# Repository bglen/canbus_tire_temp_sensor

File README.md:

# canbus_tire_temp_sensor

Tire temperature sensing with IR sensor arrays and a CAN bus interface

### To Do
* CAD enclosure
* CAN Message Data Frame Description
* Firmware
* Adjust PCB design for PCBA

## Building the Hardware
The gerber files for ordering boards can be found in the /production/ folder. A Digikey List for easy BOM ordering can be found [here](https://www.digikey.com/en/mylists/list/VY1O0SBB26).

## Usage
This device outputs thermal camera data to CAN bus. It does not include termination resistors, so only include it at the beginning or end of the network with an external 120 ohm termination resistor.

### Pinout

| Pin Number | Name     | Description                 |
| ---------- | -------- | --------------------------- |
| 1          | VCC      | Input voltage, 4.5 - 40 VDC |
| 2          | GND      | Ground                      |
| 3          | CAN_N    | CAN bus low                 |
| 4          | CAN_P    | CAN bus high                |

### Default CAN Message IDs

| Default ID     | Message            | Description                                 |
| -------------- | ------------------ | ------------------------------------------- |
| 0x700 + 1,2,3  | Data Messages      | TBD                                         |
| 0x710          | Config Messages    | Adjust Default ID, bitrate, sensor settings |

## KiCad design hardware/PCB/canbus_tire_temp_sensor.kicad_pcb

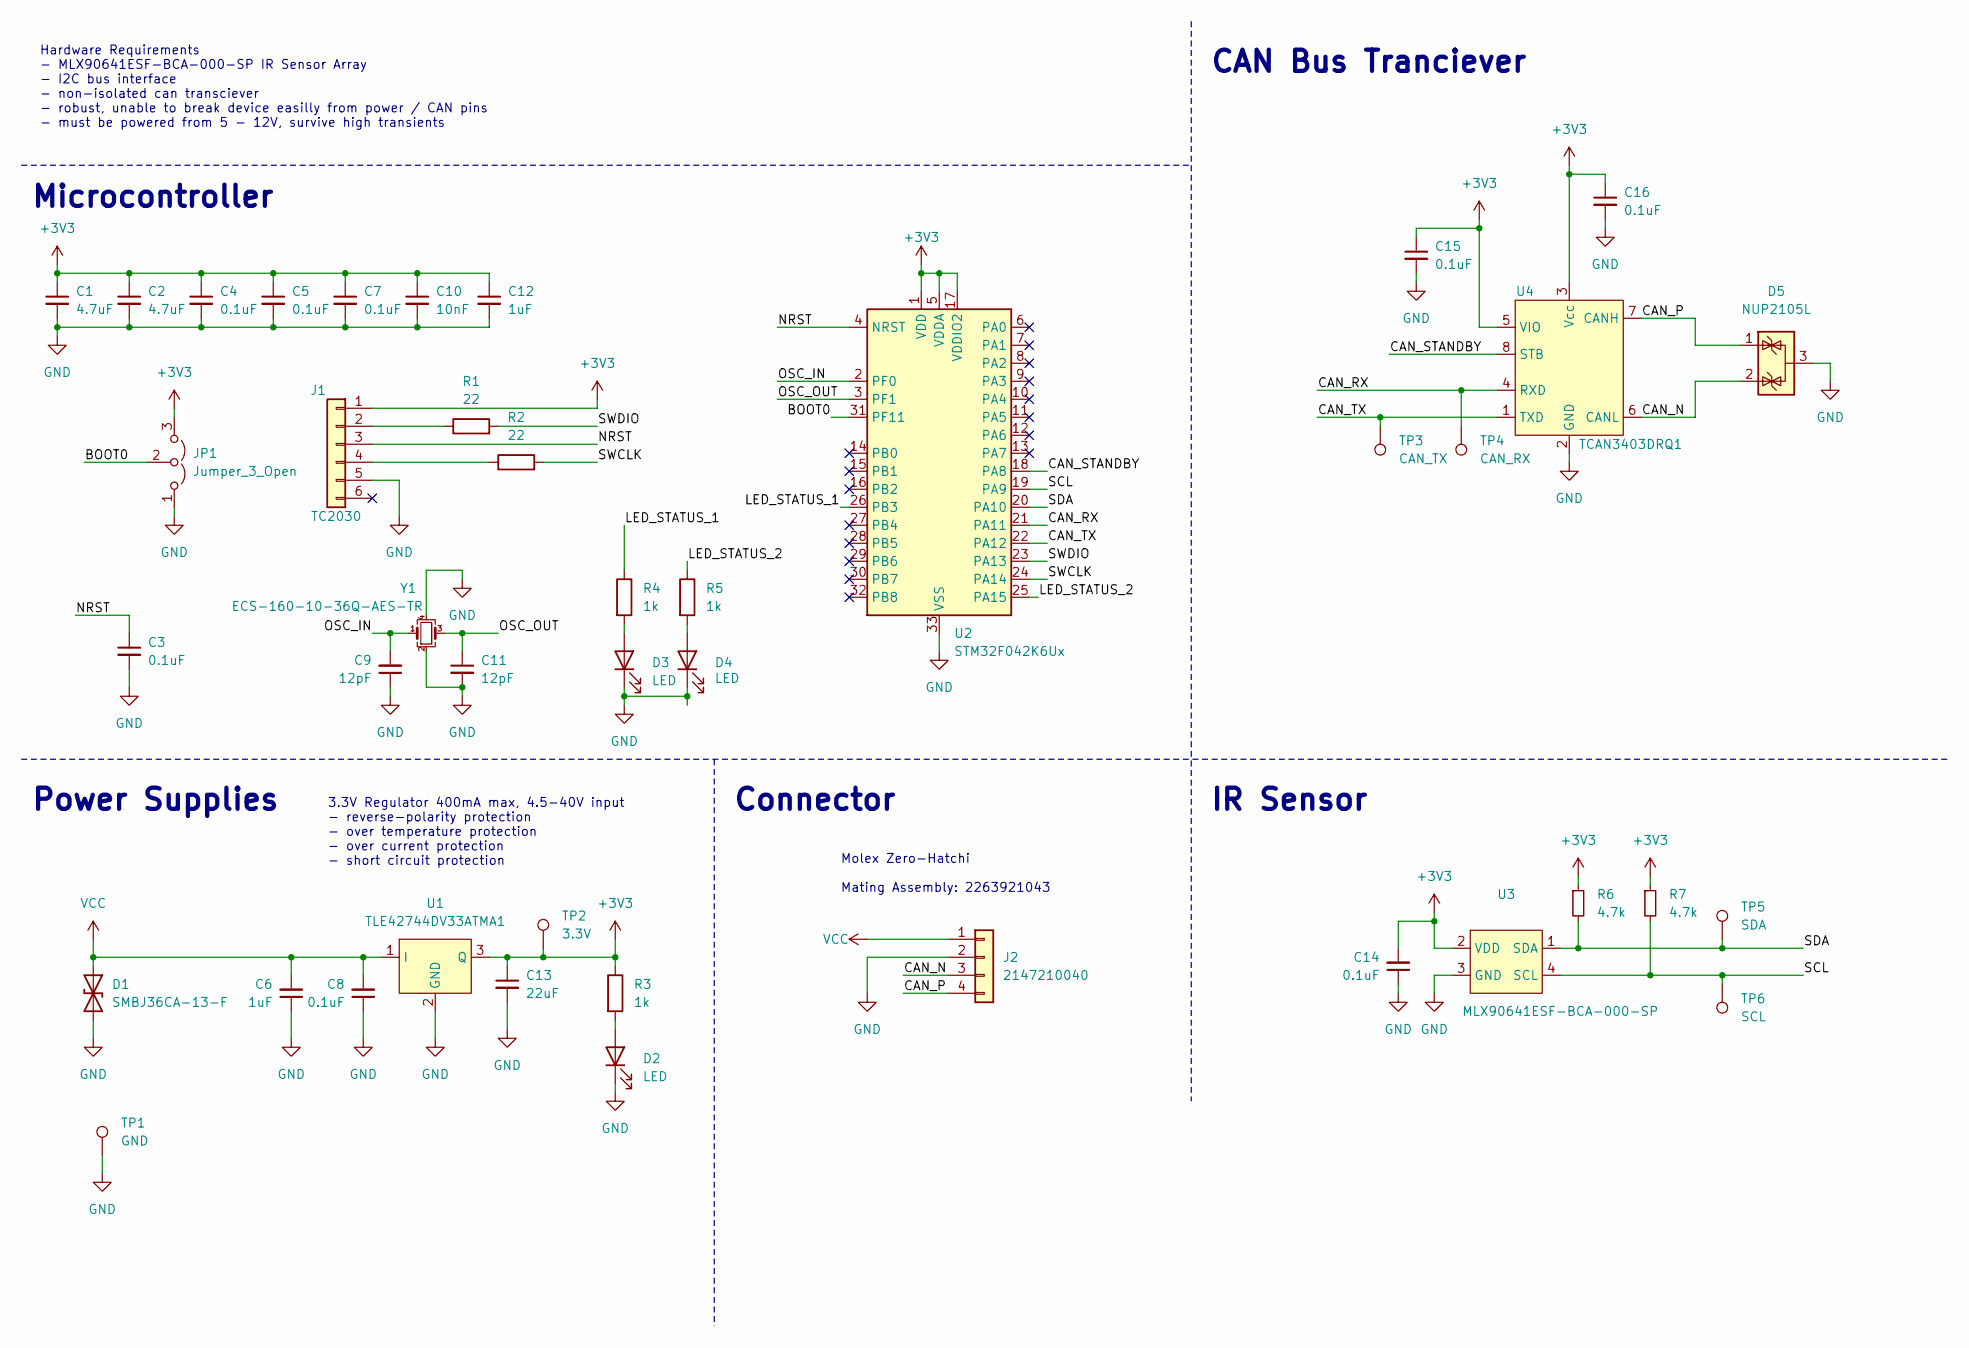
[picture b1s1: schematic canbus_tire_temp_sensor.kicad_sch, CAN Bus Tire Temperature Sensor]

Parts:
C1, C2: 4.7uF; C_0603_1608Metric
C3, C4, C5, C7, C8, C14, C15, C16: 0.1uF; C_0603_1608Metric
C6, C12: 1uF; C_0603_1608Metric
C9, C11: 12pF; C_0603_1608Metric
C10: 10nF; C_0603_1608Metric
C13: 22uF; C_0805_2012Metric
D1: SMBJ36CA-13-F; D_SMB
D2, D3, D4: LED; LED_0603_1608Metric
D5: NUP2105L; SOT-23
J1: TC2030; Tag-Connect_TC2030-IDC-NL_2x03_P1.27mm_Vertical
J2: 2147210040; Molex_Zero_Hatchi_2147210040
JP1: Jumper_3_Open; SolderJumper-3_P1.3mm_Open_RoundedPad1.0x1.5mm
R1, R2: 22; R_0603_1608Metric
R3, R4, R5: 1k; R_0603_1608Metric
R6, R7: 4.7k; R_0603_1608Metric
TP1: GND; TestPoint_Pad_D2.0mm
TP2: 3.3V; TestPoint_Pad_D2.0mm
TP3: CAN_TX; TestPoint_Pad_D1.0mm
TP4: CAN_RX; TestPoint_Pad_D1.0mm
TP5: SDA; TestPoint_Pad_D1.0mm
TP6: SCL; TestPoint_Pad_D1.0mm
U1: TLE42744DV33ATMA1; TO-252-3_TabPin2
U2: STM32F042K6Ux; QFN-32-1EP_5x5mm_P0.5mm_EP3.45x3.45mm
U3: MLX90641ESF-BCA-000-SP; MLX90641
U4: TCAN3403DRQ1; SOIC-8_3.9x4.9mm_P1.27mm
Y1: ECS-160-10-36Q-AES-TR; Crystal_SMD_2520-4Pin_2.5x2.0mm

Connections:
+3V3: C1.1, C2.1, C4.1, C5.1, C7.1, C10.1, C12.1, C13.1, C14.2, C15.1, C16.1, J1.1, JP1.3 (B), R3.1, R6.1, R7.1, TP2.1, U1.3 (Q), U2.1 (VDD), U2.5 (VDDA), U2.17 (VDDIO2), U3.2 (VDD), U4.3 (Vcc), U4.5 (VIO)
/BOOT0: JP1.2 (C), U2.31 (PF11)
/CAN_N: D5.2 (K), J2.3, U4.6 (CANL)
/CAN_P: D5.1 (K), J2.4, U4.7 (CANH)
/CAN_RX: TP4.1, U2.21 (PA11), U4.4 (RXD)
/CAN_STANDBY: U2.18 (PA8), U4.8 (STB)
/CAN_TX: TP3.1, U2.22 (PA12), U4.1 (TXD)
/LED_STATUS_1: R4.1, U2.26 (PB3)
/LED_STATUS_2: R5.1, U2.25 (PA15)
/NRST: C3.1, J1.3, U2.4 (NRST)
/OSC_IN: C9.2, U2.2 (PF0), Y1.1
/OSC_OUT: C11.1, U2.3 (PF1), Y1.3
/SCL: R7.2, TP6.1, U2.19 (PA9), U3.4 (SCL)
/SDA: R6.2, TP5.1, U2.20 (PA10), U3.1 (SDA)
/SWCLK: R2.2, U2.24 (PA14)
/SWDIO: R1.2, U2.23 (PA13)
GND: C1.2, C2.2, C3.2, C4.2, C5.2, C6.1, C7.2, C8.1, C9.1, C10.2, C11.2, C12.2, C13.2, C14.1, C15.2, C16.2, D1.2 (A2), D2.1 (K), D3.1 (K), D4.1 (K), D5.3 (A), J1.5, J2.2, JP1.1 (A), TP1.1, U1.2 (GND), U2.33 (VSS), U3.3 (GND), U4.2 (GND), Y1.2, Y1.4
unnamed: D2.2 (A), R3.2
unnamed: D3.2 (A), R4.2
unnamed: D4.2 (A), R5.2
unnamed: J1.2, R1.1
unnamed: J1.4, R2.1
VCC: C6.2, C8.2, D1.1 (A1), J2.1, U1.1 (I)

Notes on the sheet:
Power Supplies
3.3V Regulator 400mA max, 4.5-40V input - reverse-polarity protection - over temperature protection - over current protection - short circuit protection
Connector
Hardware Requirements - MLX90641ESF-BCA-000-SP IR Sensor Array - I2C bus interface - non-isolated can transciever - robust, unable to break device easilly from power / CAN pins - must be powered from 5 - 12V, survive high transients
Molex Zero-Hatchi Mating Assembly: 2263921043
CAN Bus Tranciever
IR Sensor
Microcontroller

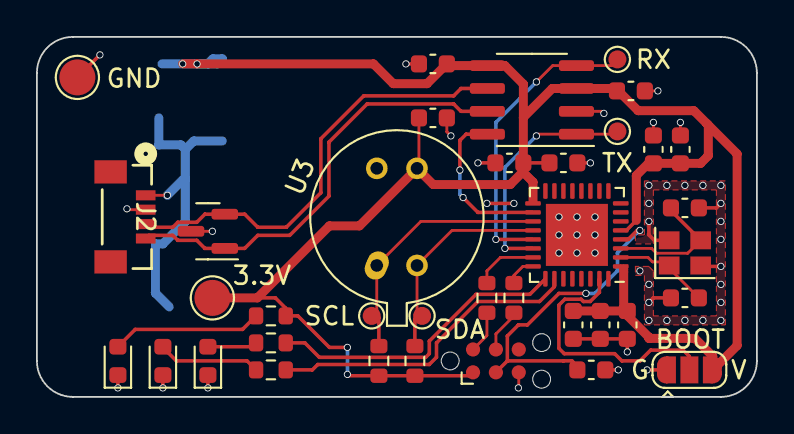
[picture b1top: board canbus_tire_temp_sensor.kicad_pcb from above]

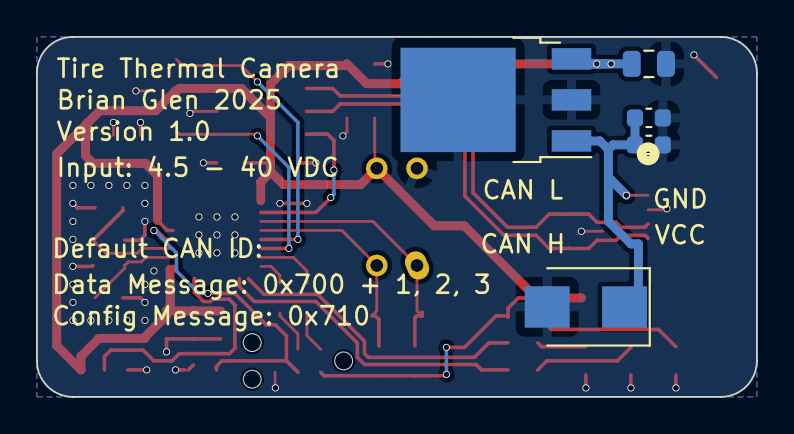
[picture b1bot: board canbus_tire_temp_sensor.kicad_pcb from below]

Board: 2 copper layers, 40.0 x 20.0 mm, 42 parts (5 on the bottom side), 23 nets.

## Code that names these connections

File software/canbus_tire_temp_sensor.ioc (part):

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Mcu.Name=STM32F042K(4-6)Ux
Mcu.Package=UFQFPN32
Mcu.UserName=STM32F042K6Ux
PA10.Mode=I2C
PA10.Signal=I2C1_SDA
PA11.Mode=CAN_Activate
PA11.Signal=CAN_RX
PA12.Mode=CAN_Activate
PA12.Signal=CAN_TX
PA13.Mode=Serial_Wire
PA13.Signal=SYS_SWDIO
PA14.Mode=Serial_Wire
PA14.Signal=SYS_SWCLK
PA15.GPIOParameters=GPIO_Label
PA15.GPIO_Label=LED_STATUS_2
PA15.Signal=GPIO_Output
PA8.GPIOParameters=GPIO_Label
PA8.GPIO_Label=CAN_STANDBY
PA8.Signal=GPIO_Input
PA9.Mode=I2C
PA9.Signal=I2C1_SCL
PB3.GPIOParameters=GPIO_Label
PB3.GPIO_Label=LED_STATUS_1
PB3.Signal=GPIO_Output
PF0-OSC_IN.Mode=HSE-External-Oscillator
PF0-OSC_IN.Signal=RCC_OSC_IN
PF1-OSC_OUT.Mode=HSE-External-Oscillator
PF1-OSC_OUT.Signal=RCC_OSC_OUT
RCC.HSE_VALUE=16000000
RCC.SYSCLKFreq_VALUE=16000000
RCC.SYSCLKSource=RCC_SYSCLKSOURCE_HSE
board=custom

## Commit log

2025-03-30 Initial STM32 Project
    Pin configuration
2025-03-30 Initial Schematic
2025-03-30 Updated footprints and ref designators
2025-03-30 initial component placement
2025-05-21 Initial board layout
2025-05-21 gerbers version 1.0
2025-05-24 Updated connector, fixed MLX footprint
2025-05-24 Rendering, removed old 3d files
2025-05-26 Updated schematic to rev 1.1
2025-06-03 version 1.2 - fixed IR sensor footprint
2025-06-03 Updated README, cleaned out prod files
2025-06-03 Updated config for board changes
2025-06-03 Fix CAN bus pin descriptions
2025-06-03 Fix CAN send limit and remove redundant comment
2025-06-03 Add documentation comments to MLX90641 driver
2025-06-11 V1.3 - Updated for cheaper JLCPCB options
    Changed via size to most common
